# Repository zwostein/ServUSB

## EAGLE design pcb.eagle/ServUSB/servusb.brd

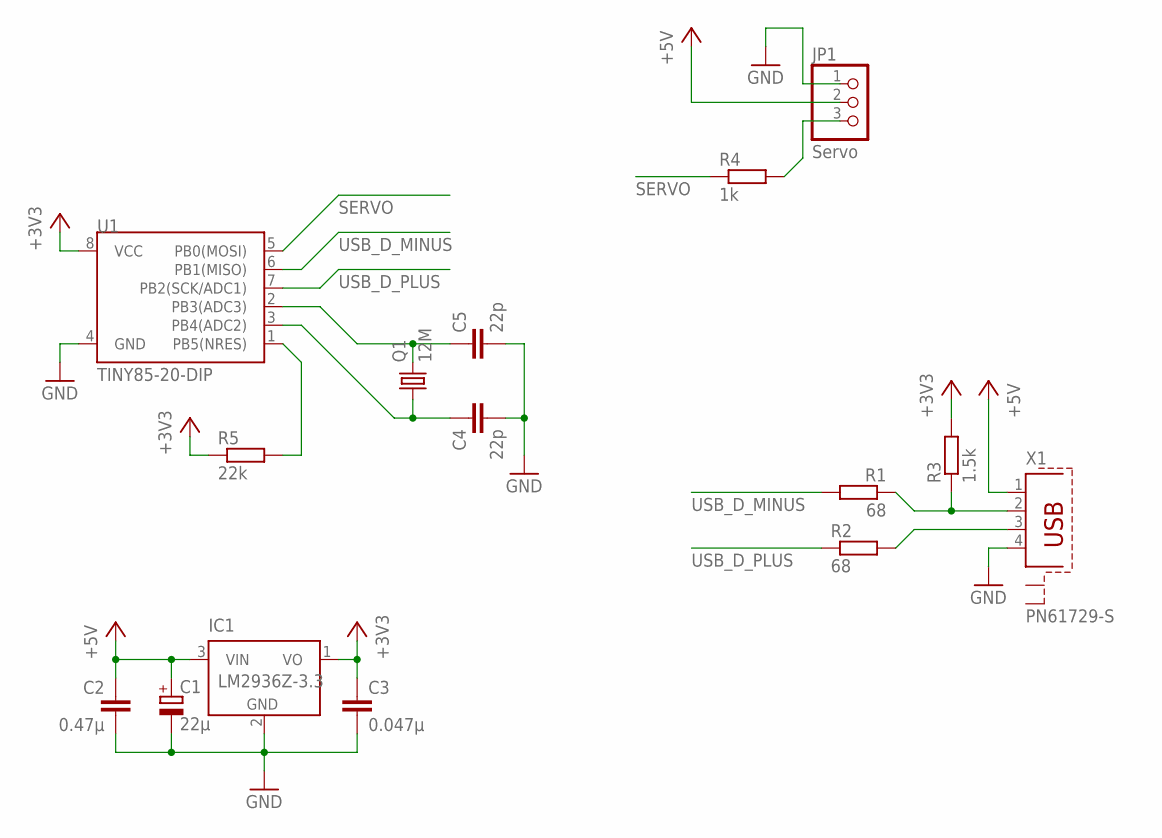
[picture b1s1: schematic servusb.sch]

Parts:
C1: 22µ; E2,5-6
C2: 0.47µ; C075-042X103
C3: 0.047µ; C050-025X075
C4, C5: 22p; C025-024X044
IC1: LM2936Z-3.3; TO92
JP1: Servo; 1X03
Q1: 12M; HC49/S
R1, R2: 68; 0204/7
R3: 1.5k; 0204/7
R4: 1k; 0204/7
R5: 22k; 0204/7
U1: TINY85-20-DIP; DIP08
X1: PN61729-S

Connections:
+3V3: C3.1, IC1.1 (VO), R3.2, R5.1, U1.8 (VCC)
+5V: C1.+, C2.1, IC1.3 (VIN), JP1.2, X1.1
GND: C1.-, C2.2, C3.2, C4.2, C5.2, IC1.2 (GND), JP1.1, U1.4 (GND), X1.4
unnamed: C5.1, Q1.2, U1.2 (PB3(ADC3))
unnamed: C4.1, Q1.1, U1.3 (PB4(ADC2))
unnamed: R5.2, U1.1 (PB5(NRES))
unnamed: R1.1, R3.1, X1.2
unnamed: R2.2, X1.3
unnamed: JP1.3, R4.2
SERVO: R4.1, U1.5 (PB0(MOSI))
USB_D_MINUS: R1.2, U1.6 (PB1(MISO))
USB_D_PLUS: R2.1, U1.7 (PB2(SCK/ADC1))

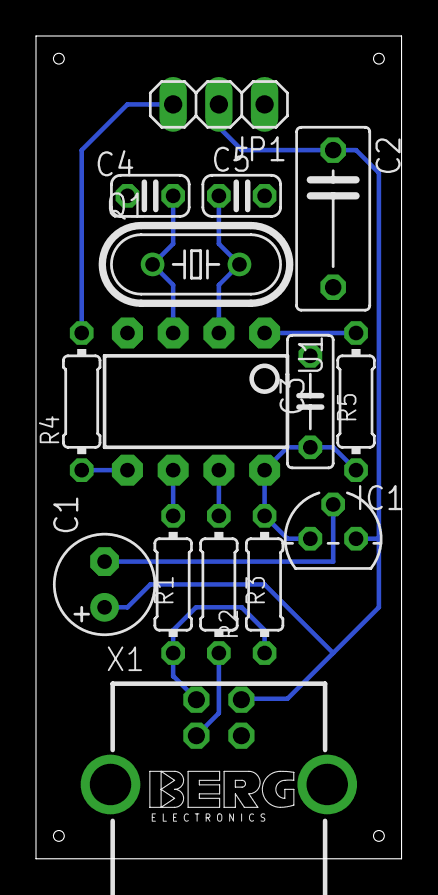
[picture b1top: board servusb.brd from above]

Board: 2 copper layers, 20.3 x 45.7 mm, 15 parts (0 on the bottom side), 12 nets.

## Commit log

2014-08-25 added .gitignore
2014-08-25 libusb
2014-08-25 cleaned up
2014-09-08 switched to getopt for better portability
2014-09-29 added PCB files
2014-09-29 renamed
2014-11-25 packaging

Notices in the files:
parts and their libraries:
SparkFun-DigitalIC: Licensing: Creative Commons ShareAlike 4.0 International - https://creativecommons.org/licenses/by-sa/4.0
